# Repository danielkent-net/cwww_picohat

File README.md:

# cwww\_picohat: Pi Pico based Dual Cool/Warm LED Lamp Controller

A Raspberry Pi Pico/Pi Pico W based controller for dual cool white / warm
white common anode LED lamps.

|KiCAD Render | Assembled Version|
|---|---|
|  |  |

This repository contains two variants: the original "hat" based design, which
is smaller and contains a connector for a dedicated user I/O board, and a
larger "board" variant that puts everything on a flat board. The board
variant is a much more mature design and is recommended if you want to try
making this yourself.

This board was designed to work with
[ESPHome](https://github.com/esphome/esphome), but could be easily programmed
with other software tools.

# License

[The hardware is licensed under the CERN Open Hardware License Version
2 - Strongly Reciprocal](LICENSE).

[ESPHome configurations are licensed under the MIT license](LICENSE-SW).

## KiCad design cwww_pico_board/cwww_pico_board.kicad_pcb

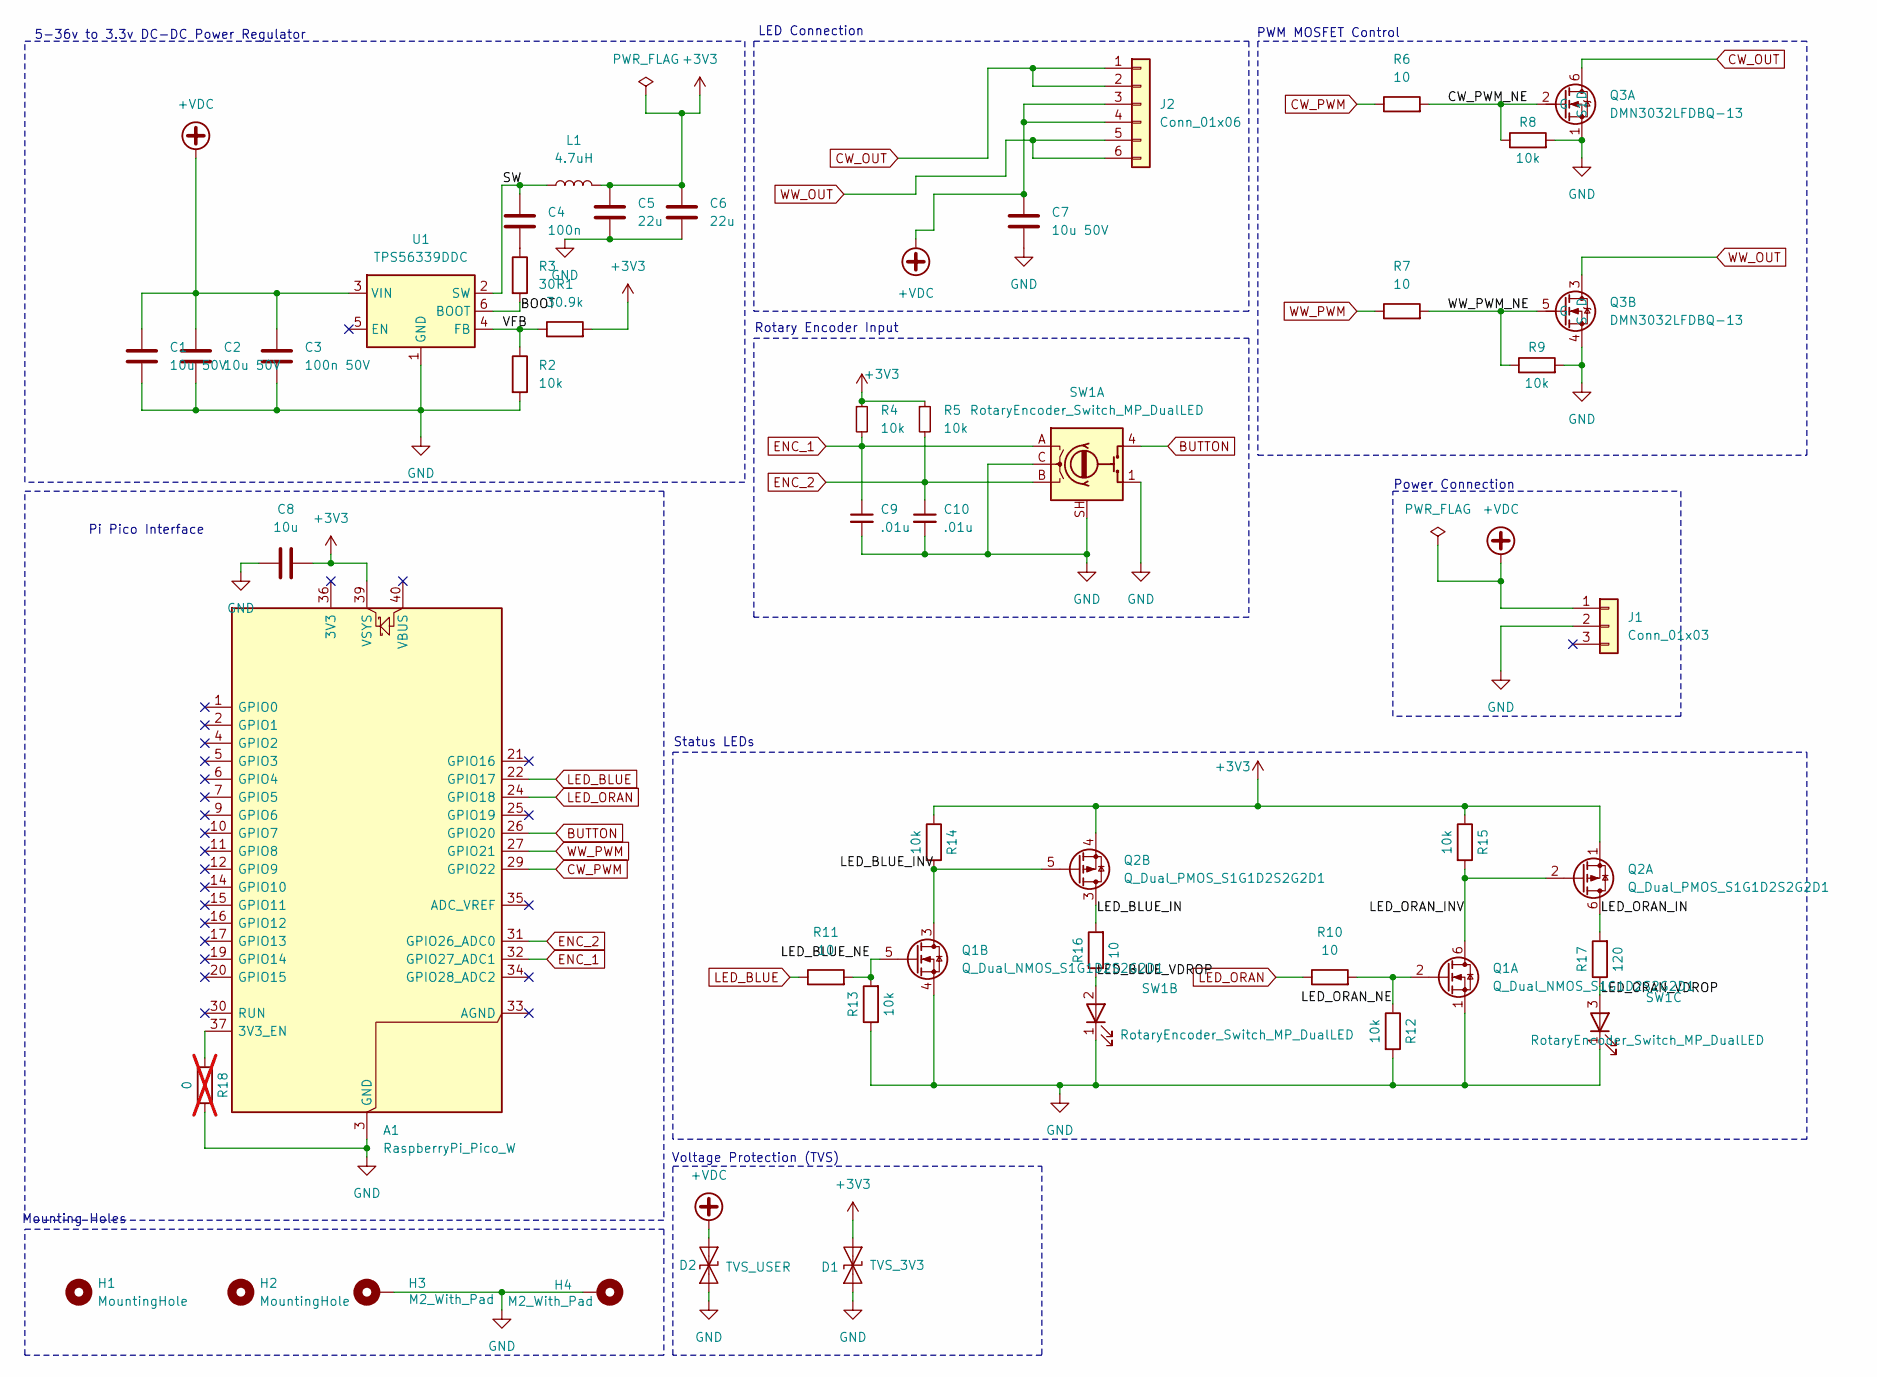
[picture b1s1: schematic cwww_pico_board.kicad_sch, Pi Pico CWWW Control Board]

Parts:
A1: RaspberryPi_Pico_W; RaspberryPi_Pico_Common_MountingHoles
C1, C2, C7: 10u 50V; C_0805_2012Metric
C3: 100n 50V; C_0805_2012Metric
C4: 100n; C_0805_2012Metric
C5, C6: 22u; C_0805_2012Metric
C8: 10u; C_0805_2012Metric
C9, C10: .01u; C_0805_2012Metric
D1: TVS_3V3; D_SOD-323
D2: TVS_USER; D_SOD-323
H1, H2: MountingHole; ZipTieHole_3.8mm
H3, H4: M2_With_Pad; MountingHole_2.2mm_M2_DIN965_Pad
J1: Conn_01x03; BarrelJack_Wuerth_6941xx301002_ShortOverhang
J2: Conn_01x06; JST_PH_S6B-PH-K_1x06_P2.00mm_Horizontal
L1: 4.7uH; INDPM3015X150N
Q1: Q_Dual_NMOS_S1G1D2S2G2D1
Q2: Q_Dual_PMOS_S1G1D2S2G2D1; SOT-363_SC-70-6
Q3: DMN3032LFDBQ-13; DMN3032LFDBQ13_OSHPark; Mouser Part Number 621-DMN3032LFDBQ-13
R1: 30.9k; R_0603_1608Metric
R2, R4, R5, R8, R9, R12, R13, R14, R15: 10k; R_0603_1608Metric
R3: 30; R_0603_1608Metric
R6, R7, R10, R11, R16: 10; R_0603_1608Metric
R17: 120; R_0603_1608Metric
R18: 0; R_0603_1608Metric; not fitted
SW1: RotaryEncoder_Switch_MP_DualLED; RotaryEncoder_Bourns_Vertical_PEL12D-4xxxF-Sxxxx
U1: TPS56339DDC; SOT-23-6

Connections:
+3V3: A1.39 (VSYS), C5.1, C6.1, C8.1, D1.1 (A1), L1.2, Q2.1 (S), Q2.4 (S), R1.2, R4.1, R5.1, R14.1, R15.1
+VDC: C1.1, C2.1, C3.1, C7.1, D2.1 (A1), J1.1, J2.3, J2.4, U1.3 (VIN)
/BOOT: R3.2, U1.6 (BOOT)
/CW_PWM_NE: Q3.2 (G), R6.2, R8.1
/LED_BLUE_IN: Q2.3 (D), R16.2
/LED_BLUE_INV: Q1.3 (D), Q2.5 (G), R14.2
/LED_BLUE_NE: Q1.5 (G), R11.2, R13.2
/LED_BLUE_VDROP: R16.1, SW1.2 (A_LED1)
/LED_ORAN_IN: Q2.6 (D), R17.2
/LED_ORAN_INV: Q1.6 (D), Q2.2 (G), R15.2
/LED_ORAN_NE: Q1.2 (G), R10.2, R12.1
/LED_ORAN_VDROP: R17.1, SW1.3 (A_LED2)
/SW: C4.1, L1.1, U1.2 (SW)
/VFB: R1.1, R2.1, U1.4 (FB)
/WW_PWM_NE: Q3.5 (G), R7.2, R9.1
BUTTON: A1.26 (GPIO20), SW1.4 (S1)
CW_OUT: J2.1, J2.2, Q3.6 (D)
CW_PWM: A1.29 (GPIO22), R6.1
ENC_1: A1.32 (GPIO27_ADC1), C9.1, R4.2, SW1.A
ENC_2: A1.31 (GPIO26_ADC0), C10.1, R5.2, SW1.B
GND: A1.3 (GND), A1.8 (GND), A1.13 (GND), A1.18 (GND), A1.23 (GND), A1.28 (GND), A1.38 (GND), C1.2, C2.2, C3.2, C5.2, C6.2, C7.2, C8.2, C9.2, C10.2, D1.2 (A2), D2.2 (A2), H3.1, H4.1, J1.2, Q1.1 (S), Q1.4 (S), Q3.1 (S1), Q3.4 (S), R2.2, R8.2, R9.2, R12.2, R13.1, R18.2, SW1.1 (GND), SW1.C, SW1.SH (MP), U1.1 (GND)
LED_BLUE: A1.22 (GPIO17), R11.1
LED_ORAN: A1.24 (GPIO18), R10.1
unnamed: A1.37 (3V3_EN), R18.1
unnamed: C4.2, R3.1
WW_OUT: J2.5, J2.6, Q3.3 (D)
WW_PWM: A1.27 (GPIO21), R7.1

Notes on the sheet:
Power Connection
5-36v to 3.3v DC-DC Power Regulator
PWM MOSFET Control
Pi Pico Interface
LED Connection
Mounting Holes
Rotary Encoder Input
Voltage Protection (TVS)
Status LEDs

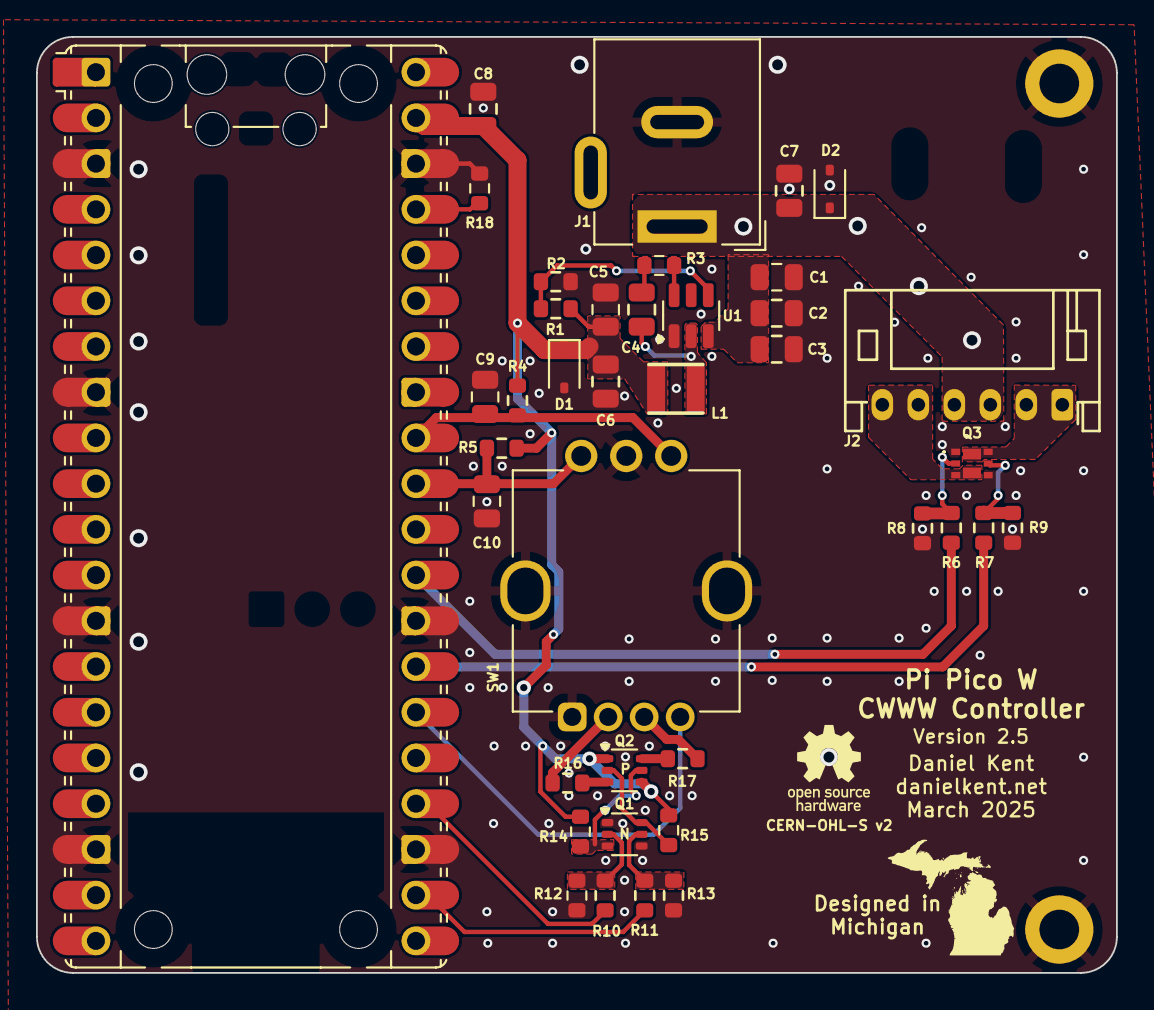
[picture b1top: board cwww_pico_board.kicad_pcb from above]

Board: 2 copper layers, 60.0 x 52.0 mm, 43 parts (0 on the bottom side), 27 nets.

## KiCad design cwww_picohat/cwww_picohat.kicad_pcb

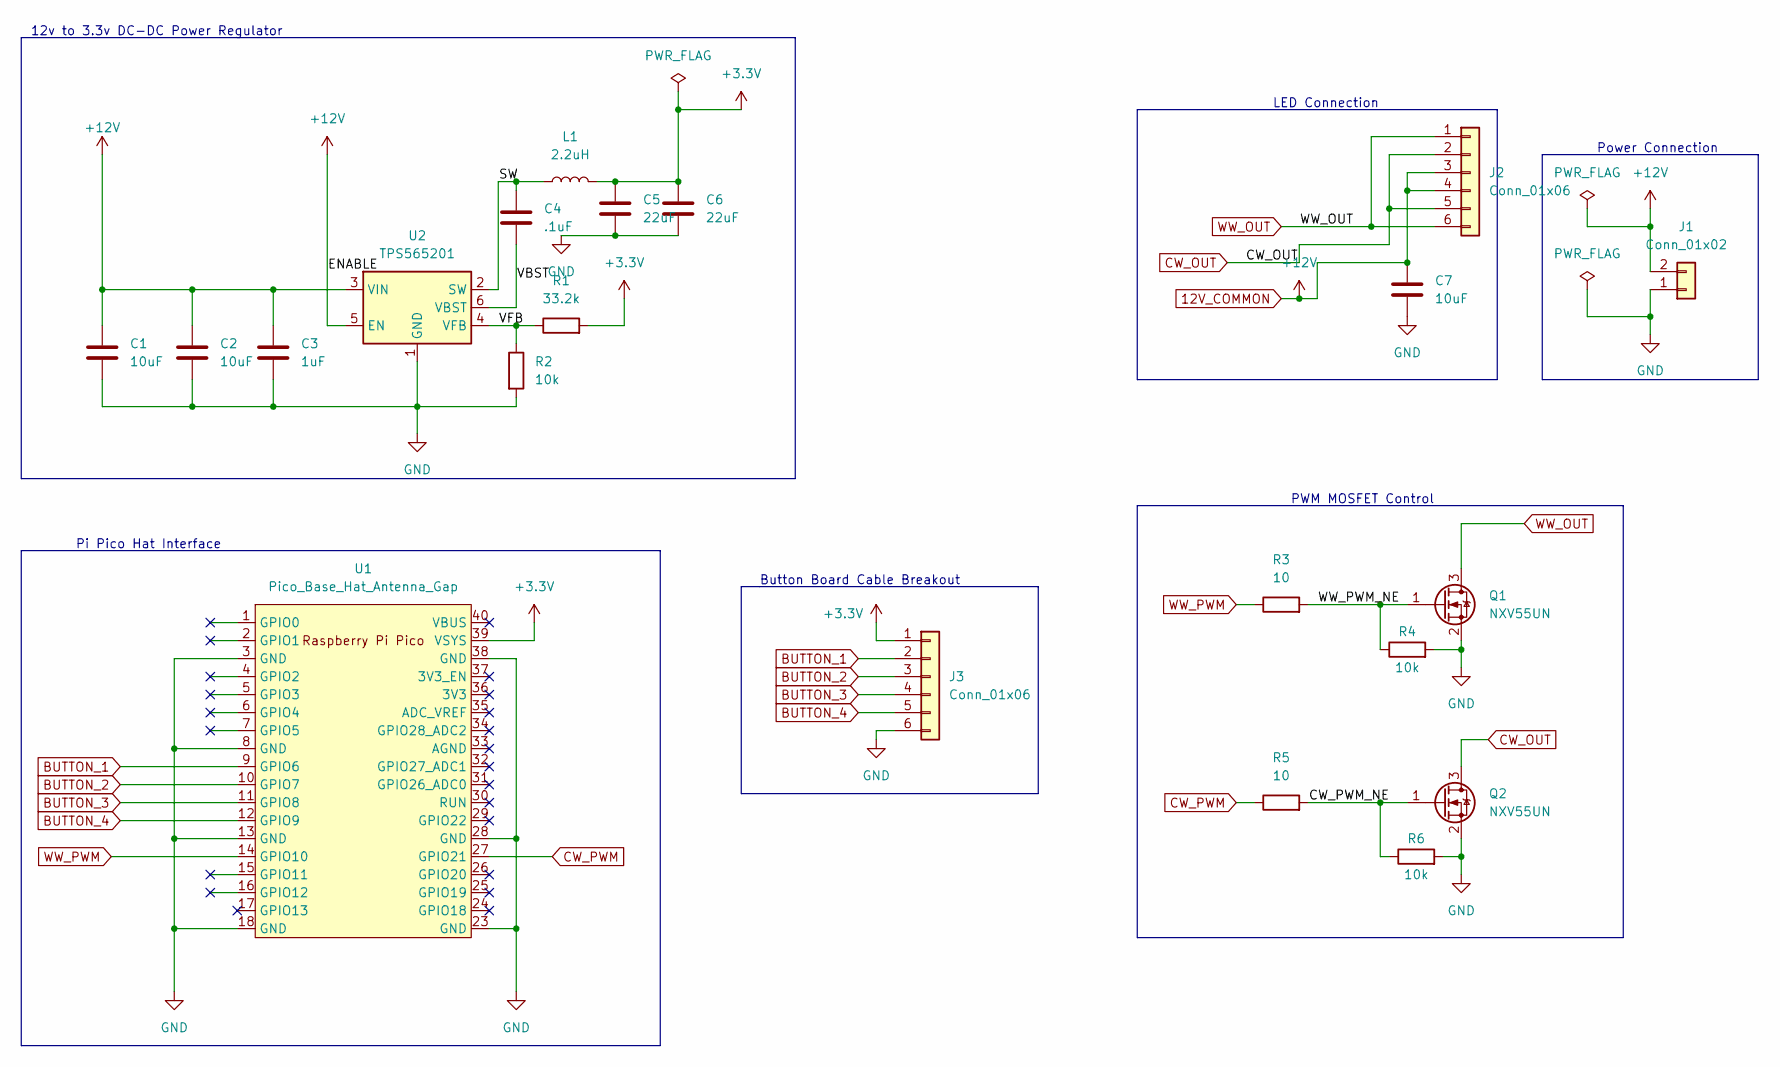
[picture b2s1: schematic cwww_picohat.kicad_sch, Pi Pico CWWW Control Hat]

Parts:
C1, C2, C7: 10uF; C_0805_2012Metric_Pad1.18x1.45mm_HandSolder
C3: 1uF; C_0805_2012Metric_Pad1.18x1.45mm_HandSolder
C4: .1uF; C_0603_1608Metric_Pad1.08x0.95mm_HandSolder
C5, C6: 22uF; C_0805_2012Metric_Pad1.18x1.45mm_HandSolder
J1: Conn_01x02; JST_PH_S2B-PH-K_1x02_P2.00mm_Horizontal
J2: Conn_01x06; JST_PH_S6B-PH-K_1x06_P2.00mm_Horizontal
J3: Conn_01x06; JST_PH_B6B-PH-K_1x06_P2.00mm_Vertical
L1: 2.2uH; L_1210_3225Metric_Pad1.42x2.65mm_HandSolder
Q1, Q2: NXV55UN; SOT-23-3
R1: 33.2k; R_0603_1608Metric_Pad0.98x0.95mm_HandSolder
R2, R4, R6: 10k; R_0603_1608Metric_Pad0.98x0.95mm_HandSolder
R3, R5: 10; R_0603_1608Metric_Pad0.98x0.95mm_HandSolder
U1: Pico_Base_Hat_Antenna_Gap; Partial Pico Hat with Antenna Gap
U2: TPS565201; SOT-23-6

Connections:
12V_COMMON: C1.1, C2.1, C3.1, C7.1, J1.2, J2.3, J2.4, U2.3 (VIN), U2.5 (EN)
+3V3: C5.1, C6.1, J3.1, L1.2, R1.2, U1.39 (VSYS)
/CW_PWM_NE: Q2.1 (G), R5.2, R6.1
/SW: C4.1, L1.1, U2.2 (SW)
/VBST: C4.2, U2.6 (VBST)
/VFB: R1.1, R2.1, U2.4 (VFB)
/WW_PWM_NE: Q1.1 (G), R3.2, R4.1
BUTTON_1: J3.2, U1.9 (GPIO6)
BUTTON_2: J3.3, U1.10 (GPIO7)
BUTTON_3: J3.4, U1.11 (GPIO8)
BUTTON_4: J3.5, U1.12 (GPIO9)
CW_OUT: J2.2, J2.5, Q2.3 (D)
CW_PWM: R5.1, U1.27 (GPIO21)
GND: C1.2, C2.2, C3.2, C5.2, C6.2, C7.2, J1.1, J3.6, Q1.2 (S), Q2.2 (S), R2.2, R4.2, R6.2, U1.3 (GND), U1.8 (GND), U1.13 (GND), U1.18 (GND), U1.23 (GND), U1.28 (GND), U1.38 (GND), U2.1 (GND)
WW_OUT: J2.1, J2.6, Q1.3 (D)
WW_PWM: R3.1, U1.14 (GPIO10)

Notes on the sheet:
Power Connection
12v to 3.3v DC-DC Power Regulator
PWM MOSFET Control
Pi Pico Hat Interface
LED Connection
Button Board Cable Breakout

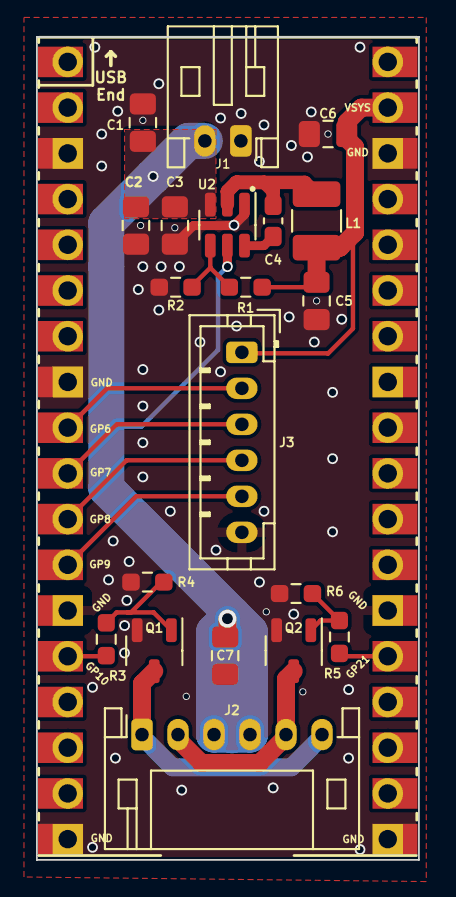
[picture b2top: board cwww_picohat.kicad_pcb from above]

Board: 2 copper layers, 21.2 x 45.7 mm, 21 parts (0 on the bottom side), 16 nets.

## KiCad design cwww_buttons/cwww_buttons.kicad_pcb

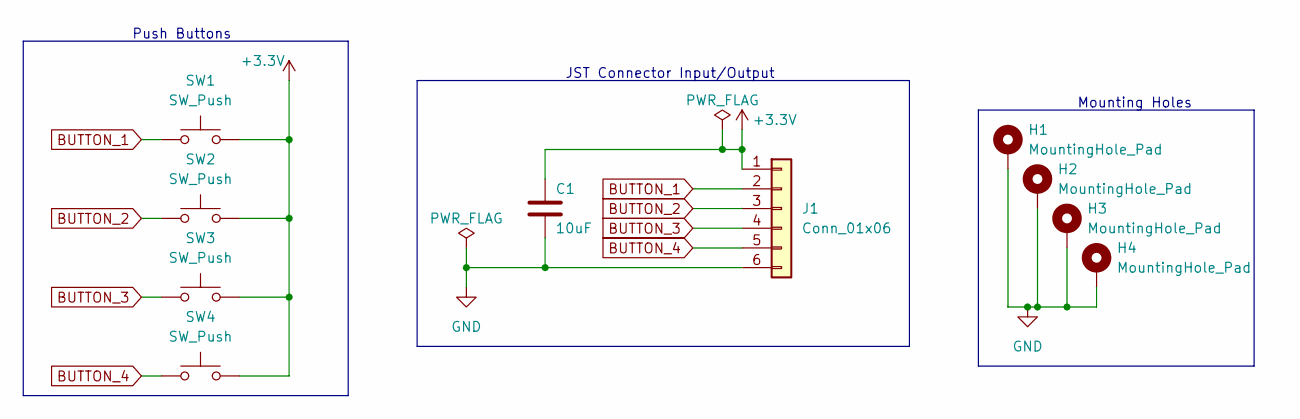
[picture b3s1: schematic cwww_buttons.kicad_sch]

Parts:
C1: 10uF; C_0805_2012Metric_Pad1.18x1.45mm_HandSolder
H1, H2, H3, H4: MountingHole_Pad; MountingHole_2.2mm_M2_DIN965_Pad
J1: Conn_01x06; JST_PH_B6B-PH-K_1x06_P2.00mm_Vertical
SW1, SW2, SW3, SW4: SW_Push; SW_Push_1P1T_NO_6x6mm_H9.5mm

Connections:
+3V3: C1.1, J1.1, SW1.2, SW2.2, SW3.2, SW4.2
BUTTON_1: J1.2, SW1.1
BUTTON_2: J1.3, SW2.1
BUTTON_3: J1.4, SW3.1
BUTTON_4: J1.5, SW4.1
GND: C1.2, H1.1, H2.1, H3.1, H4.1, J1.6

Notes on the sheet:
Mounting Holes
JST Connector Input/Output
Push Buttons

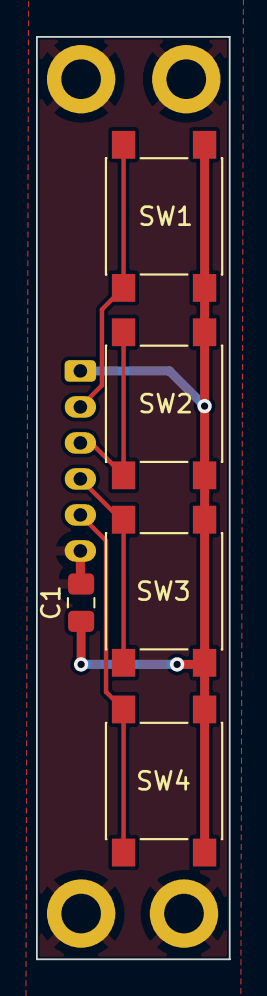
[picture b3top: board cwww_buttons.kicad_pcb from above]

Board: 2 copper layers, 10.7 x 51.2 mm, 10 parts (1 on the bottom side), 6 nets.

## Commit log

2025-04-10 First public release of CWWW boards
2025-04-10 Fixed README typo

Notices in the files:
cwww_buttons/cwww_buttons.kicad_pcb:
CERN-OHL-S v2
cwww_pico_board/cwww_pico_board.kicad_sch:
License: CERN-OHL-S v2
